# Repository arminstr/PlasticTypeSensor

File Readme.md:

# WARNING: Due to personal reasons the development on this project was stopped 1 year ago. 

## Infos about this repository
It contains all necessary information to rebuild the MEMS-Based plasitc type sensor which was meant to be the follow up of reremeter. 
The files an information is ~ 1 year old and only published now due to large interest from openrecycling.com community. 

## Plastic Type Sensor Testing and Evaluation
Run the python scripts using Visual Studio Code for Maximum Compatibility.
If somebody wants to create a colab or jupyter notebook pull requests are always welcome.

The first measurement results look promising! The following plot shows the measurement data in this git repo.

## Help needed on data processing!
Please support the plastic type sensor project by submitting pull requests to the data evaluation software.

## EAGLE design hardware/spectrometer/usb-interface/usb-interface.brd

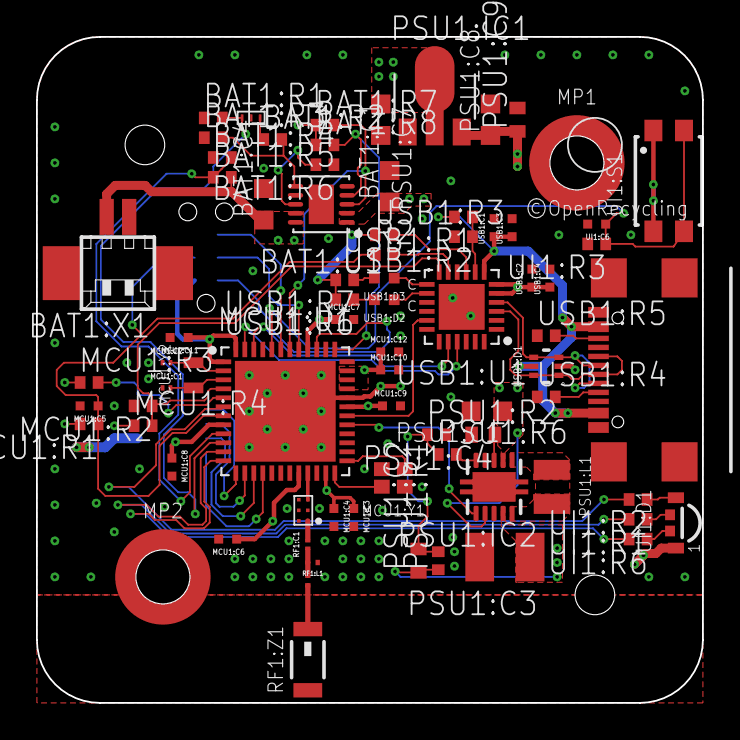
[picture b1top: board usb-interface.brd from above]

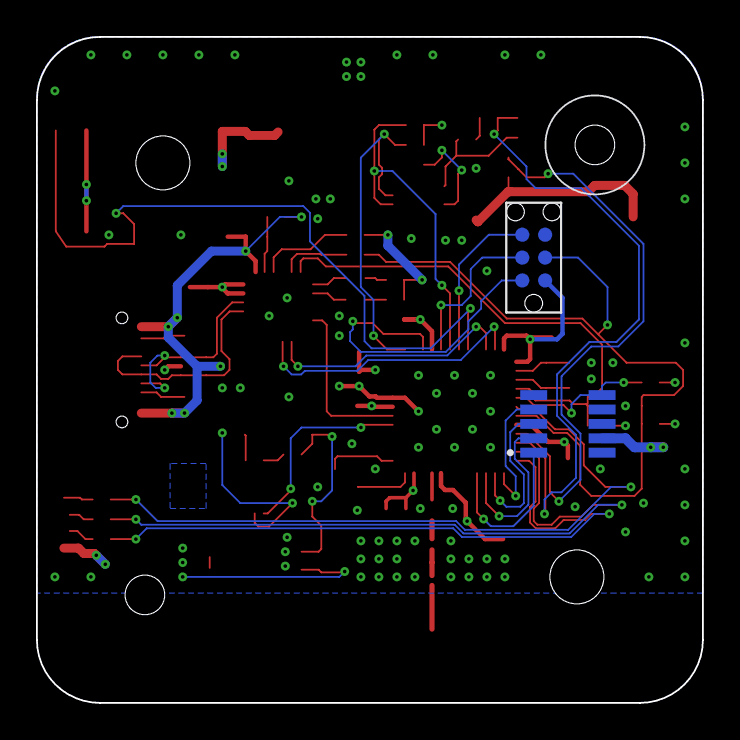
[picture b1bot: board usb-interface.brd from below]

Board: 4 copper layers, 37.0 x 37.0 mm, 78 parts (2 on the bottom side), 59 nets.

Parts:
BAT1:C1, BAT1:C4: 4.7uF; C0603K
BAT1:Q1: CSD18541F5
BAT1:R1, BAT1:R3, BAT1:R4, BAT1:R5, BAT1:R6, BAT1:R7, BAT1:R8: 10k; R0402
BAT1:R2: 1k; R0402
BAT1:U1: MCP73833; SON50P300X300X100-11T140X220N
BAT1:X1: 53261-02
MCU1:C1, MCU1:C2: 9pF; WCAP-CSRF_0201
MCU1:C3: 100 pF; WCAP-CSGP_0402
MCU1:C4, MCU1:C5, MCU1:C6, MCU1:C7, MCU1:C8, MCU1:C9, MCU1:C11, MCU1:C12: 100 nF; WCAP-CSGP_0402
MCU1:C10: 1 µF; WCAP-CSGP_0402
MCU1:FLT1: MLPF-WB55-01E3; CSP-6
MCU1:R1, MCU1:R2, MCU1:R3: 100k; R0402
MCU1:R4: 0R; R0402
MCU1:U1: STM32WB30CE; QFN50P700X700X60-49T560N
MCU1:X1: TC2030-NLTC2030-IDC-NL-FP; TC2030-NL
MCU1:Y1: NX2016SA-32MHz; WE-XTAL_IQXC-42
MCU1:Y2: 32.768kHz; WE-XTAL_IQXC-25
MP1, MP2: 9774015243; WA-SMSI_9774015243
PSU1:C1, PSU1:C7, PSU1:C8: 4.7uF; C0603K
PSU1:C2: 33pF; C0402
PSU1:C3: 4.7uF/25V; C1210
PSU1:C4: 47nF; C0402
PSU1:C9: 100nF; C0402
PSU1:IC1: MCP170333MB; SOT89
PSU1:IC2: TPS61080QFN10; S-PDSO-N10
PSU1:L1: 4.7uH; WE-LQS_2512
PSU1:R1: 437k; R0402
PSU1:R2: 49.9k; R0402
PSU1:R6: 100R; R0402
R2: 0R; R0402
RF1:C1: 1.2pF; WCAP-CSRF_0201
RF1:L1: 2.7nH; WE-TCI_0201
RF1:L2: 3.3nH; WE-TCI_0201
RF1:Z1: 2400-2500 MHz; WE-MCA_7488930245
UI1:C6: 100 nF; WCAP-CSGP_0402
UI1:D1: 155124M173200; WL-SFSW_1204
UI1:R1: 120R; R0402
UI1:R2: 270R; R0402
UI1:R3: 100k; R0402
UI1:R6: 43R; R0402
UI1:S1: 434331045822; 4343X10458XX
USB1:C1, USB1:C2: 100 nF; WCAP-CSGP_0402
USB1:C3, USB1:C4: 1 µF; WCAP-CSGP_0402
USB1:D1: 5Vdc; WE-TVS_SOT563
USB1:D2: 150040GS73240; WL-SMCC_0402
USB1:D3: 150040YS73240; WL-SMCC_0402
USB1:R1: 22.1k; R0402
USB1:R2: 47.5k; R0402
USB1:R3, USB1:R6, USB1:R7: 1k; R0402
USB1:R4, USB1:R5: 5.1k; R0402
USB1:U1: CP2102N; QFN50P400X400X80-25T255N
USB1:X1: USB4110; USBCGCT
X1: 524651071

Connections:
+3V3: MCU1:C3.2, MCU1:C4.2, MCU1:C6.2, MCU1:C7.2, MCU1:C8.2, MCU1:C9.2, MCU1:C10.2, MCU1:C11.2, MCU1:C12.2, MCU1:R1.2, MCU1:R3.1, MCU1:R4.1, MCU1:U1.1, MCU1:U1.8, MCU1:U1.20, MCU1:U1.23, MCU1:U1.31, MCU1:U1.33, MCU1:U1.34, MCU1:U1.35, MCU1:U1.40, MCU1:U1.48, MCU1:X1.1, PSU1:C8.1, PSU1:C9.1, PSU1:IC1.3, UI1:D1.1, UI1:S1.1, UI1:S1.3
+5V: BAT1:C1.1, BAT1:U1.1, BAT1:U1.2, USB1:C1.2, USB1:C3.2, USB1:D1.5, USB1:R1.2, USB1:U1.7, USB1:X1.A4B9, USB1:X1.B4A9
BAT1:+3V3: BAT1:R7.1, BAT1:R8.1
BAT1:N$1: BAT1:Q1.3, BAT1:R2.1
BAT1:PROG: BAT1:R2.2, BAT1:R3.2, BAT1:U1.6
BAT1:THERM: BAT1:R6.2, BAT1:U1.8
BLUE: MCU1:U1.12, UI1:R6.2
BOOT0: MCU1:R2.1, MCU1:R4.2, MCU1:U1.4, USB1:U1.12
CLK: MCU1:U1.14, X1.3
CS: MCU1:U1.13, X1.4
ENABLE_12V: MCU1:U1.29, PSU1:IC2.6
GND: BAT1:C1.2, BAT1:C4.2, BAT1:Q1.2, BAT1:R1.1, BAT1:R3.1, BAT1:R4.1, BAT1:R6.1, BAT1:U1.5, BAT1:U1.11, BAT1:X1.2, MCU1:C1.1, MCU1:C2.1, MCU1:C3.1, MCU1:C4.1, MCU1:C5.1, MCU1:C6.1, MCU1:C7.1, MCU1:C8.1, MCU1:C9.1, MCU1:C10.1, MCU1:C11.1, MCU1:C12.1, MCU1:FLT1.2, MCU1:FLT1.4, MCU1:FLT1.5, MCU1:FLT1.6, MCU1:R2.2, MCU1:U1.22, MCU1:U1.32, MCU1:U1.49, MCU1:U1.P$1, MCU1:U1.P$2, MCU1:U1.P$3, MCU1:U1.P$4, MCU1:U1.P$5, MCU1:U1.P$6, MCU1:U1.P$7, MCU1:U1.P$8, MCU1:U1.P$9, MCU1:U1.P$10, MCU1:U1.P$11, MCU1:U1.P$12, MCU1:X1.5, MCU1:Y1.2, MCU1:Y1.4, PSU1:C1.2, PSU1:C3.2, PSU1:C4.2, PSU1:C7.2, PSU1:C8.2, PSU1:C9.2, PSU1:IC1.1, PSU1:IC2.4, PSU1:IC2.8, PSU1:IC2.PP, PSU1:IC2.PP@1, PSU1:IC2.PP@2, PSU1:R2.2, RF1:L1.1, UI1:C6.1, UI1:R3.2, USB1:C1.1, USB1:C2.1, USB1:C3.1, USB1:C4.1, USB1:D1.2, USB1:R2.2, USB1:R4.1, USB1:R5.1, USB1:U1.2, USB1:U1.25, USB1:U1.P$1, USB1:U1.P$2, USB1:X1.A1B12, USB1:X1.B1A12, USB1:X1.SHIELD@1, USB1:X1.SHIELD@2, USB1:X1.SHIELD@3, USB1:X1.SHIELD@4, X1.5, X1.6, X1.8, X1.9
GREEN: MCU1:U1.11, UI1:R1.2
I_LIM: BAT1:Q1.1, BAT1:R1.2, MCU1:U1.10
MCU1:N$1: MCU1:FLT1.3, MCU1:U1.21
MCU1:OSC32_IN: MCU1:C2.2, MCU1:U1.2, MCU1:Y2.2
MCU1:OSC32_OUT: MCU1:C1.2, MCU1:U1.3, MCU1:Y2.1
MCU1:OSC_IN: MCU1:U1.25, MCU1:Y1.1
MCU1:OSC_OUT: MCU1:U1.24, MCU1:Y1.3
MCU1:SWCLK: MCU1:U1.41, MCU1:X1.4
MCU1:SWDIO: MCU1:U1.39, MCU1:X1.2
MCU1:SWO: MCU1:U1.43, MCU1:X1.6
MISO: MCU1:U1.15, X1.2
MOSI: MCU1:U1.16, X1.1
NRST: MCU1:C5.2, MCU1:R1.1, MCU1:U1.7, MCU1:X1.3, R2.1
NSHDN: MCU1:R3.2, MCU1:U1.5, X1.10
PSU1:N$1: PSU1:IC2.1, PSU1:L1.1
PSU1:N$2: PSU1:IC2.10, PSU1:L1.2
PSU1:N$3: PSU1:C4.1, PSU1:IC2.3
PSU1:N$4: PSU1:C2.2, PSU1:R1.2, PSU1:R2.1, PSU1:R6.1
PSU1:N$5: PSU1:IC2.5, PSU1:R6.2
RED: MCU1:U1.6, UI1:R2.2
RF: MCU1:FLT1.1, RF1:C1.2
RF1:FEED: RF1:L2.1, RF1:Z1.1
RF1:MATCH: RF1:C1.1, RF1:L1.2, RF1:L2.2
RX: MCU1:U1.47, USB1:U1.21
STAT1: BAT1:R7.2, BAT1:U1.3, MCU1:U1.42
STAT2: BAT1:R8.2, BAT1:U1.4, MCU1:U1.37
SUSPENDED: MCU1:U1.30, USB1:U1.17
SWITCH: MCU1:U1.44, UI1:C6.2, UI1:R3.1, UI1:S1.2, UI1:S1.4
TX: MCU1:U1.46, USB1:U1.20
UI1:N$1: UI1:D1.2, UI1:R6.1
UI1:N$2: UI1:D1.3, UI1:R1.1
UI1:N$3: UI1:D1.4, UI1:R2.1
USB1:+3V3: USB1:C2.2, USB1:C4.2, USB1:R3.1, USB1:R6.2, USB1:R7.2, USB1:U1.5, USB1:U1.6
USB1:CC1: USB1:R4.2, USB1:X1.A5
USB1:CC2: USB1:R5.2, USB1:X1.B5
USB1:CP_NRST: USB1:R3.2, USB1:U1.9
USB1:D_N: USB1:D1.3, USB1:D1.4, USB1:U1.4, USB1:X1.A7, USB1:X1.B7
USB1:D_P: USB1:D1.1, USB1:D1.6, USB1:U1.3, USB1:X1.A6, USB1:X1.B6
USB1:N$1: USB1:D3.2, USB1:R7.1
USB1:N$2: USB1:D2.2, USB1:R6.1
USB1:RXT: USB1:D3.1, USB1:U1.13
USB1:TXT: USB1:D2.1, USB1:U1.14
USB1:VBUS: USB1:R1.1, USB1:R2.1, USB1:U1.8
USB_NRST: R2.2, USB1:U1.11
V+: PSU1:C2.1, PSU1:C3.1, PSU1:IC2.9, PSU1:R1.1, X1.7
VBAT: BAT1:C4.1, BAT1:R5.2, BAT1:U1.9, BAT1:U1.10, BAT1:X1.1, PSU1:C1.1, PSU1:C7.1, PSU1:IC1.2@1, PSU1:IC2.2, PSU1:IC2.7
VBAT_SENSE: BAT1:R4.2, BAT1:R5.1, MCU1:U1.9

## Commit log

2022-12-05 added hardware simultion and embedded software
2022-12-05 Added description of calibration folder.

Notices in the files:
hardware/spectrometer/usb-interface/usb-interface.brd:
©OpenRecycling
parts and their libraries:
Wurth_Assembly_WA-SMSI: Copyright: Würth Elektronik
